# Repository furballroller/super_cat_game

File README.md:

# super_cat_game

> [!CAUTION]
> The current hardware version is [hardware_v1](hardware_v1)!! Anyway, is my first PCB project, so neither version is very good. It may be cost-inefficient and buggy.

> [!WARNING]
> **if regenerating production files from KICAD, the LCSC Part # in the BOM and component orientations in CPL may be incorrect. Make sure to double check part numbers and orientation in JLCPCB before paying** I don't know how to fix it and had to directly edit BOM.csv :<

> [!TIP]
> these banners are so cool lol

_Final product:_

- [_3D-printed case on Onshape_](https://cad.onshape.com/documents/4ded436d6b7f683e9c68b6fa/w/fe5cc562122e090332767be7/e/b2ba9b935da609d900851709?renderMode=0&uiState=6a58e4a5db7545b8e7dbac50) (proper assembly instructions below)
- [_KiCAD Project_](hardware_v1)
- [_Arduino Sketches_](software) (PlatformIO IDE)

Cat silhouette traced from this photo: ID <a href="https://www.dreamstime.com/cat-mid-air-jump-white-coloured-patches-jumping-down-against-yellow-wall-image115652480">115652480</a> @ <a href="https://www.dreamstime.com/lazaroctavian_info">Octavian Mihai Lazar</a> | <a href="https://www.dreamstime.com/">Dreamstime.com</a>

## backstory

So basically my friend had a cat, and I was just getting into arduino electronics, so I wanted to make a chasing game for the both of them! I ended up deciding on a pressure-sensitive LED mat, for an interactive laser-pointer kind-of game, with wifi connectivity for convenience. It could be nice to use regularly to keep your pets fit, but really this is just a fun beginner project to me.

Then, in between reels, I discovered Fallout, a 2026 hardware hackathon for 13-18yos backed by Hack Club. I was drawn in by the promise of full project funding and a free trip to Shenzhen, and was enthralled by the experienced and helpful community ready to help. I would highly recommend Hack Club hackathons like this if you're new/intermediate like me and within the age range :>

The scope expanded when I realised that there's so much more potential with my setup! I used a powerful ESP32 S3 N16R8 Devkit, so I broke out the pins for prototyping. You can hook up any peripherals you want for your game! Like, with a [3D printed kibble dispenser](https://electronoobs.com/tutorial/3d-printed-arduino-cat-feeder), you could implement scheduled feeding and dispense treats as an in-game currency :>

But you can program anything, not just for a cat! Chess online/locally would be easy and super fun! Maybe even something like [Osu](https://osu.ppy.sh/), make use of the full spectrum of colours! You might even want to host an online multiplayer game...

## overview

This project hardwires a pressure-sensitive LED mat to a powerful general-purpose devkit, intended for making inuitive arcade-style games (for a cat, if you'd like! :> )

I used Arduino to code up a simple cat game ([Arduino sketch](software/cat_game)), where a laser dot darts around, avoids people, and resets the game when caught. To use this, just upload the code to the devkit (using it's built-in USB-C port), plug it into the PCB, then plug the PCB into the wall!

The devkit opens the project to endless posibilities, including bluetooth game controllers, network games, and over-the-air coding for easy game dev ([template Arduino sketch with ArduinoOTA](software/template+OTA)). This project is meant to function as a very cool extension of the microcontroller, for those who might want to jump straight into making games using this touch interface.

### specs

- ~45*45cm play area
  - 14*14 Velostat pressure sensor matrix
  - 13*13 WS2812B LED matrix (very low resolution tho)
- Wifi/Bluetooth capability
  - Cheap ESP32 S3 N16R8 Devkit clone off [AliExpress](https://www.aliexpress.com/item/1005008790513258.html)
- Broken-out devkit pins and 5V power supply for any peripherals you might like to add
  - e.g. [3D printed kibble dispenser](https://electronoobs.com/tutorial/3d-printed-arduino-cat-feeder)

### cost

[Overall BOM.csv](bom.csv) | [PCB BOM.csv](hardware_v1/production/bom.csv)

The overall BOM represents what I plan to order: 5 populated PCB boards (JLCPCB minimum order quantity), but only 1 housing/mat/devkit. Though, I did include a laptop charger and the LED strips that I already have. This comes out to 111.83 USD.

I didn't include tools (not consumed) like soldering equipment and a 3D printer, but I did approximate the cost of consumables like solder, tape rolls, screws and filament.

#### Per unit

|Cost (USD)|Stuff|
|--|--|
|14.11|Power supply|
|22.15|Electronics|
|2.32|Housing|
|33.32|Mat|

Excluding shipping, it's about 71.90 USD per unit.

<!--
## big_picture
the mat should roll up

-->

### hardware

<!-- a flowchart -->

I decided to use a USBC PD laptop charger as the PSU since it's quite common and versatile and it's not too expensive.

The velostat matrix is connected with two 45cm lengths of 16-way IDC cables (not shown in CAD). One individual line will be cut, stripped, and stuck to the sensor lines at regular intervals along the mat, 14 horizontally and 14 vertically. There's more detail in the assembly walkthrough below.

#### Velostat pressure sensor matrix

The rest of the system is quite self-explanatory except for the Velostat pressure sensor matrix, so I'll try my best to explain. There's a good video of it by [MarcoReps on YouTube](https://www.youtube.com/watch?v=0uPZwMg5B3k).

Velostat is a thin plastic sheet with electrical resistance that decreases as it is pressed or deformed.

Each "sensor" works by sandwiching a square of Velostat between perpendicular strips of conductive fabric tape, such that it acts as a resistor between them.

When the Velostat is compressed, the resistance between the two strips decreases. Connecting one tape to 3.3V through a normal resistor (e.g. 10k Ohms) and the other to GND, the circuit becomes a voltage divider between the Velostat and the normal resistor. The microcontroller can read the voltage at this point (relative to GND) to figure out the resistance of the Velostat, which tells you approximately how much pressure is on it!

Along one long conductive strip, multiple perpendicular strips can be laid across with Velostat between, creating a line of sensors. By connecting all the perpendicular lines to a multiplexer's channels, they are all left in a high-impedance state except the selected channel. The normal resistor and ADC pin can be connected on the single output of the multiplexer, so they can be reused when the channel is switched.

Conventional diagram

Another way to show the same circuit:

The matrix in the mat is 14 conductive lines crossed with 14 perpendicular lines, making a total of 14^2=196 "sensors." It's the same as the line of sensors, but there are multiple lines of sensors, with one ground connection each. The ground connections are controlled by another multiplexer, only allowing one line to be active at once.

This is a 4 by 4 example. Multiplexer 1 picks the line of sensors connected to GND, and multiplexer 2 picks the sensor from that line to read.

The real mat works using two 16 channel multiplexers (CD74HC4067) on the PCB: the ESP32 specifies a channel, the multiplexers switch to the corresponding Velostat sensor, then the ESP32 takes a reading through it's ADC pin. Instead of the normal resistor, there is a potentiometer (variable resistor) that allows you to adjust sensitivity.

This is how the sensors are tiled

### code

[My example sketches:](software) (currently untested)

- [press_light](software/press_light): intended to be a test of function, that should simply light up LEDs around where you press. This would be great for making sure the hardware is behaving, or as a fun starting point if you want to experiment with code and get the hang of Arduino.
- [cat_game](software/cat_game): a simple cat game where the computer controls a red laser-pointer-like dot to avoid people.
- [template](software/template): an empty template for your project! I set up some useful functions in functions.cpp and put all the initialisation code in for you.
- [template+OTA](software/template+OTA): same as [template](software/template), but I also set up [ArduinoOTA](https://github.com/JAndrassy/ArduinoOTA). I think it's really cool that you can upload code wirelesly like magic! ([a cool tutorial page](https://www.programmingelectronics.com/arduinoota/))

I used PlatformIO on Visual Studio Code to write my Arduino programs for the microcontroller. This may sound convoluted, but I did it this way because Arduino programs are easy to write (compared to industrial languages) but Arduino IDE is horrible!

If you want to use Arduino IDE, you can quite easily copy-paste my code into the IDE. For a given project folder in [software](software), you just kinda paste the stuff from functions.cpp first, then the stuff from main.cpp... it may take a bit of fiddling around though, so I would recommend looking into PlatformIO (after getting used to it, I find it way way better :>)

I used [FastLED](https://github.com/fastled/fastled) to control the WS2812B neopixels

## assembly

<!--    -->

I thought it was cool to include the little thumb, and the vents are accurate too! They're like LHS/RHS prints from a cat grabbing the case or something :>
Also, the USB port is on a 45 degree angle so the wire leaves perpendicular to the mat.

I'll touch on the key features of the design below. For more info, see the 3D model for this is in [my Onshape doc](https://cad.onshape.com/documents/4ded436d6b7f683e9c68b6fa/w/fe5cc562122e090332767be7/e/b2ba9b935da609d900851709?renderMode=0&uiState=6a58e4a5db7545b8e7dbac50), under the tab "boxV1"
(my bad for the bad organisation, I'm still learning CAD)  

If you want to change the tolerances (they're untested), I haven't tried, sorry if something is inaccurate. It may be best to change the tolerances in your slicer.
> [!TIP]
> the Onshape link might not work. I had to click it, then **Ctrl+X Ctrl+V Enter** from the address bar

### electronics

I contained the circuit in a PCB attached to the corner of the mat, and I've also desgined a 3D-printed housing for it.

The whole project runs off an ESP32 S3 N16R8 microcontroller devkit, which is like an Arduino but better (in my opinion)

[On Aliexpress](https://www.aliexpress.com/item/1005008790513258.html)
(**I would recommend getting "S3 KIT" because the screw terminals are very handy, but I put the board by itself into the BOM**)

When choosing a microcontroller, I noticed that a lot of clone (knockoff) ESP32 S3 devkits, including the one I bought, have the antenna port but also an antenna built into the PCB. I think they give you the option to change to an external antenna by doing a bit of soldering, but by default it is connected to the onboard antenna.

#### PCB

<!--    -->

> [!CAUTION]
>
> - Ignore the capacitor going off the edge, the EasyEDA model is wrong
> - The two parallel rows of vertical pin headers (for the devkit) should be female, again the EasyEDA model is wrong

About the design:

- JL1 and JR1 hold the ESP32 devkit
- The USB-C is for power only
- JLED1 is for the LED strip
- JPWR1 is 5V power for any peripherals you might want to add
- The IDC sockets are for the pressure-sensing data lines
- The fancy ICs are just CD74HC4067 multiplexers for selecting the pressure-sensing channel to read
- The potentiometer is for adjusting the sensitivity of the pressure sensing (it's part of a voltage divider)
- U1 is a logic level converter for the LEDs.

Regarding soldering: I designed the PCB to be hand-soldered, hence the abundance of THT and the large 0805 capacitors/resistors. My only concerns are the SSOP 74HC4067 and 6-pin USB-C port, but other than that the rest should be beginner friendly, from what I can gather. I'm thinking of going to my local makerspace to solder this. In Melbourne, Library at the Dock has one equipped with a digital microscope, flux/solder/wick, and  Hakko FX-888 soldering stations, all free of charge. Maybe be careful around ESD, I'll update on my degree of success when I build it.

#### housing

<!--  -->

I'm not very good at 3D CAD either, but this should work... I think  
The design is quite self-explanatory, but below are some key features that I thought I should highlight:

On the base, there is a cutout for those holes on the mat. The holes are truncated cones, inspired by [this video by BV3D](https://youtu.be/zaphoWIwSGI). 
I designed my case to work with 3M screws, and the truncated cones means you can use machine screws or self-tapping (I think)

The base supports the PCB with a few stilts through the holes in the PCB, again using M3 truncated cones. The smaller stilts give some support to the IDC connectors, which I expect may require some force to plug in and out.

The top fits on the bottom with M3 screws, and features holes for IDC, the LED strip, the USB-C power port, optional 5V power lines, and the broken-out GPIO from the devkit. Also there are (very stylish) vents :>

There's also a lid that slides onto the top, so the devkit is protected but can be accessed easily during game development. 
I included a cool thinner section where the onboard LED is, so the status light should look like a cat's paw.

### sensor_mat

> [!TIP]
> You'll see two holes in the top-right corner of the mat. These fit M3 screw heads, and should help anchor the PCB to the mat.

1. The LED strips

I used 13 LED long sections of 30 LED/m WS2812B individually addressable LEDs
With pads on either side, each section is about 43.333mm long (theoretically)  
[Similar product on AliExpress](https://www.aliexpress.com/item/1005007989207832.html)
(**MAKE SURE THE SPACING IS 30 LEDs/m; I'd recommend buying 2 "3m 30 IP30"**)

There are 13 of these sections, forming a 13*13 grid (169 LEDs)
The ends can be soldered together with jumper wires, preferably with stranded wire, like so:

<figure>

	<figcaption>(don't crease too much tho!)</figcaption>
</figure>

2. The popsicle sticks  

I used 2mm thick, 18mm wide popsicle sticks (jumbo craft sticks)  
[My local option (Australia)](https://www.officeworks.com.au/shop/officeworks/p/kadink-jumbo-craft-sticks-natural-50-pack-showk0137)

In the CAD, I made very long, 18mm-wide rectangles for simplicity. 
They represent the area that should be filled with popsicle sticks. 
It may be useful to trim off the rounded ends for a fuller surface, but the space could alternatively be filled with hot glue for better adhesion.

They will be adhered together with the conductive tape that goes on top (see below). 
They should be adhered to the LED strip with high-temperature hot glue or silicone (not being lazy! it's good for sticking to wood and flex-PCB, trust). 
Please ensure hot glue doesn't get under the popsicle sticks, as this may affect the pressure detection and make the mat lumpy. 

<figure>  
	 
	<figcaption>Try smushing the glue into the corner where the edge of the popsicle sticks meets the LED's flex-PCB</figcaption>
</figure>

3. Conductive fabric tape (bottom)  

I used 0.1mm thick, 8mm wide conductive fabric tape. This acts as the bottom layer of the velostat matrix.  
[Similar product on AliExpress](https://www.aliexpress.com/item/1005007568611729.html)  
(**I'd recommend buying 1 "8mm"**)

The tape sticks onto the wood to connect it together. If this isn't sturdy enough, the sticks can keep their rounded ends, and hot glue can help hold them together (in the gap made by the rounded ends)

An IDC wire needs to be attached to one end of each strip, so I recommend the following:

Leave a 1-2cm tape overhang

Peel the stripped IDC wire away from the rest and press it here. for extra security, you could wrap the tape around the entire row of IDC wires.

Press another section of tape here, sticking the sticky sides together and securing the wire's insulation and popsicle stick together

Wrap the main tape over the other strip and the wire (ensure it has contact with both the insulation and the bare metal, and press it into the crevices and flush to the bottom of the mat

4. Velostat

I used a 0.1mm thick, 280mm square sheet of velostat, cut up into ~18mm squares (this stuff is expensive!!)  
[My local option (Australia)](https://www.pakronics.com.au/products/pressure-sensitive-conductive-sheet-velostat-linqstat-ada1361)

The squares will be adhered to the popsicles with thin-film double-sided tape, with two 4mm wide sections flanking the conductive tape running down the middle of the popsicles.

It is important that the tape is as thin or thinner than the velostat (≤0.1mm), or it may squish instead of the velostat, lowering the sensitivity, and so resolution, of pressure readings.

[Double-sided tape on AliExpress](https://www.aliexpress.com/item/1005012157309588.html)  
(**I'd recommend buying 1 "5mm"**)

5. Conductive fabric tape (top)

This layer is sticky-side-up, so in real life you would stick it onto the top EVA first (see below). Please make sure the tape is aligned such that it doesn't touch the bottom layer directly anywhere, only conducting through the Velostat squares.

An IDC wire needs to be attached just like in the other layer, so I would recommend the same strategy, but wrapped upwards around the EVA. The ugly tape overhangs on top of the EVA will be covered by electrical tape later.

6. Frosted plastic sheet (EVA)

I used a ~1mm thick, 450mm square of EVA plastic intended to line drawers.  
[My local option (Australia)](https://www.rejectshop.com.au/p/drawer-and-shelf-liner-45x150cm)

The top layer of conductive tape should be stuck to the bottom of this sheet, on the smooth side. This EVA layer can be adhered to the bottom construction with electrical tape, not just because it's easy to design, but because of it's suitable properties. The mat is designed to loosely roll up for easy transport/storage, requiring flexibility, and the edges must be soft to keep flying fingers/paws safe around the mat :)

## the_past

> [!CAUTION]
> I cobbled V0 together from backups so maybe double check whether it works if you plan to build it. e.g. there's no copper exclusion around the antenna :<

Just a quick note about the [hardware_v0](hardware_v0) and [hardware_v1](hardware_v1), I just uploaded v0 so you can see a previous design I made. I wanted to preserve more ESP32 GPIO pins, so I used counter ICs to cycle through the MUX channels of the sensor grid. This would've allowed me to step through each channel with just one clock pin per counter, compared to the 4 pins per counter I would've needed to control the MUX channel directly. It wouldn't have added much time either, as the counter works even faster than a digitalWrite()! Sending one clock pulse might even be more efficient than using Arduino to update the state of 4 pins... anyway, I decided to remove the counters in V1 to save board space and money, seeing as there are so many available GPIO anyway lol :>

## the_future

Some ideas I have:

- multiplexing/charlieplexing/shift registers with regular LEDs to replace expensive neopixels
- using an ESP32 S3 WROOM SOC module for a smaller and cheaper PCB
- using a library like NeoPixelBus instead of FastLED to make the Arduino code faster/efficient
- somehow allowing IDC to attach/detatch without needing to unscrew the lid, for portability/storage

Lemme know if you've got any suggestions!
My email: [aydeny8k@gmail.com](mailto:aydeny8k@gmail.com)

## references

The Velostat pressure matrix idea: [Youtube video by MarcoReps](https://www.youtube.com/watch?v=0uPZwMg5B3k)

Truncated-cone screw holes idea: [Youtube video by BV3D](https://youtu.be/zaphoWIwSGI)

Sliding lid shape: [Wuodan0 on Thingiverse](https://www.thingiverse.com/thing:5201077)

[FastLED](https://github.com/fastled/fastled) Arduino library

[ArduinoOTA](https://github.com/JAndrassy/ArduinoOTA) Arduino library

[easyeda2kicad.py](https://github.com/uPesy/easyeda2kicad.py) Python script

Pictures annotated in Google Drawings

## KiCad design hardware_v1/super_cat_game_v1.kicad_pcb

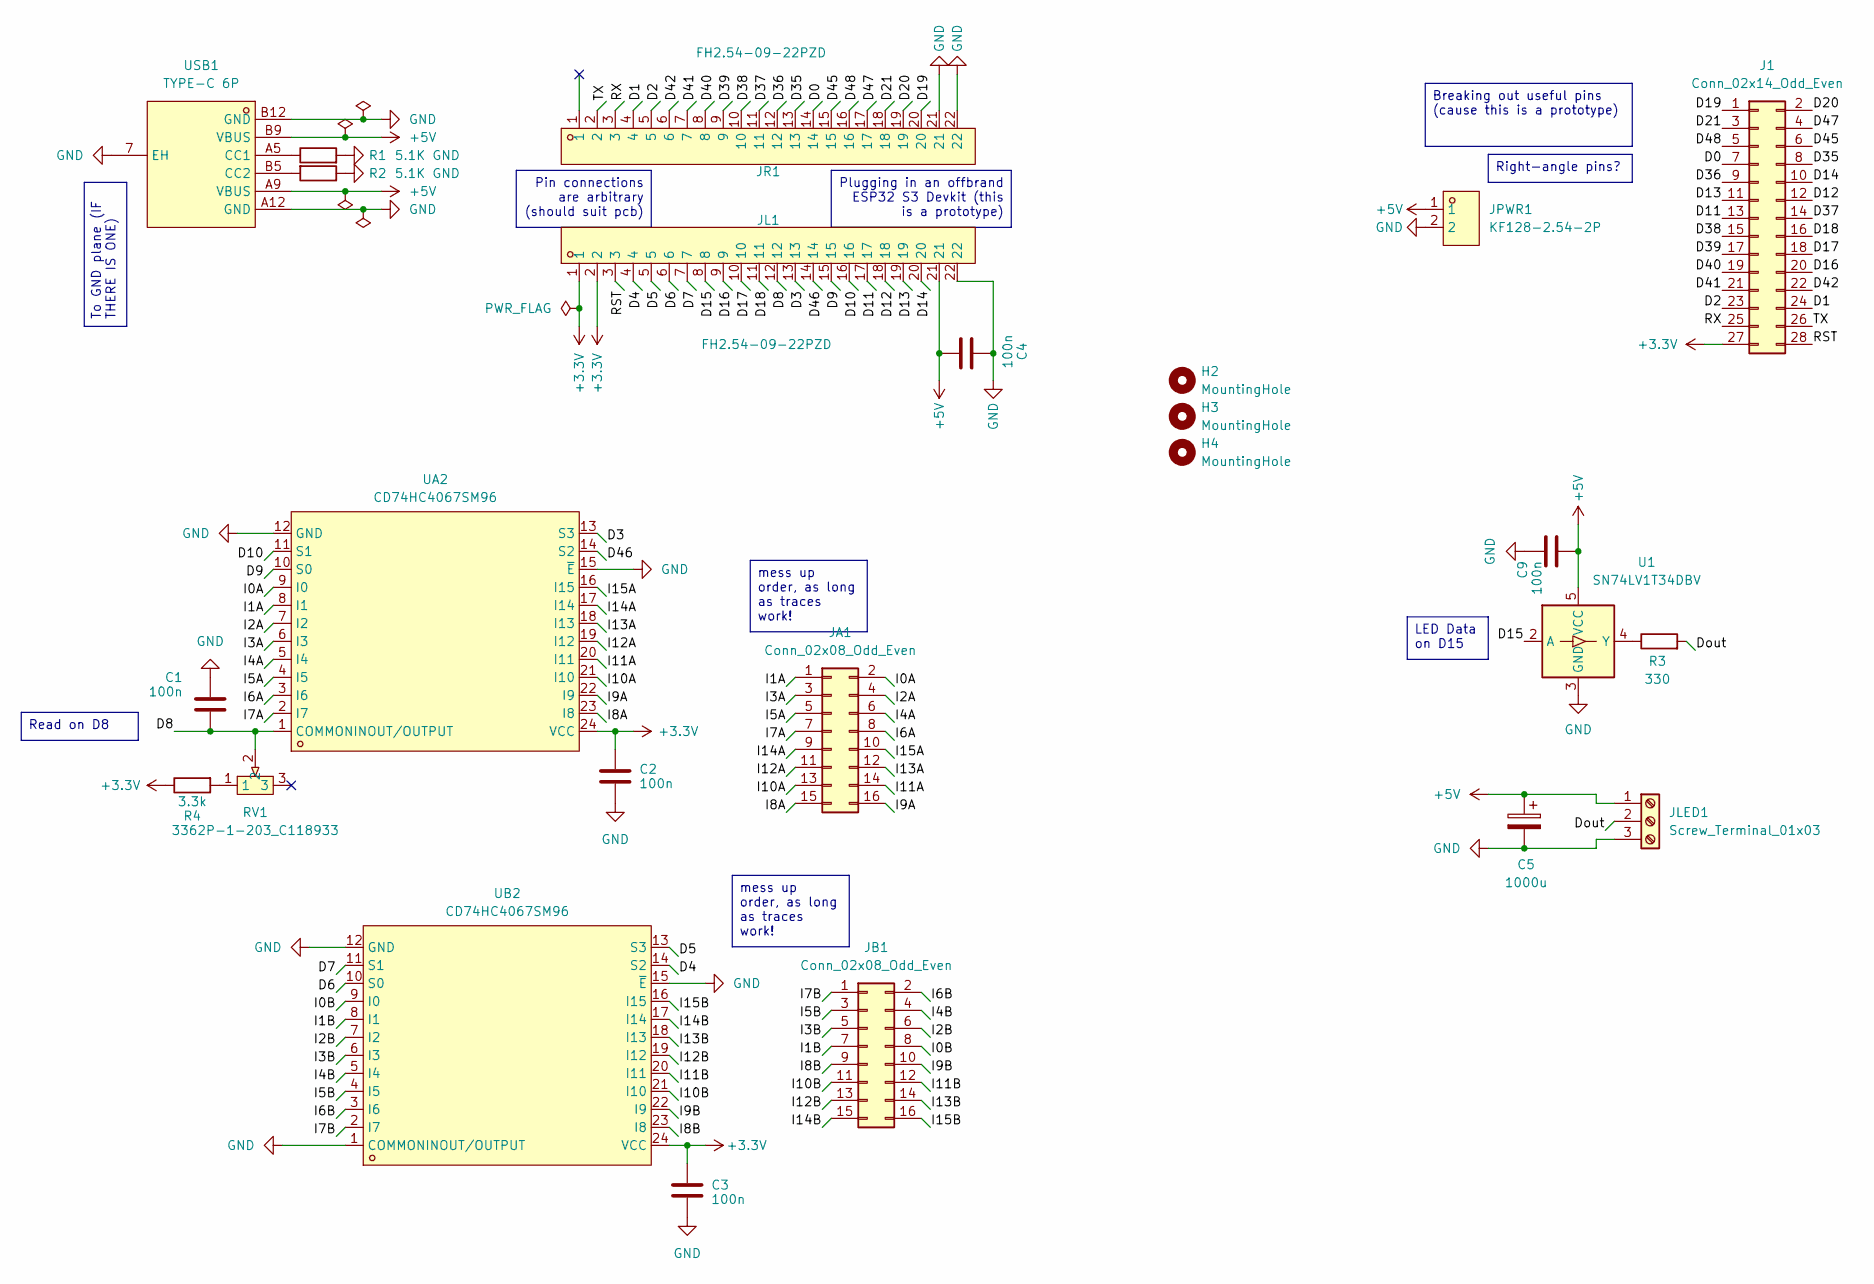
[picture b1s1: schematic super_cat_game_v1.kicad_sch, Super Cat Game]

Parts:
C1, C2, C3, C9: 100n; C_0805_2012Metric_Pad1.18x1.45mm_HandSolder; JLC_3DModel 32fe2cf9314f444ca2785a33c2db7189
C4: 100n; C_0805_2012Metric_Pad1.18x1.45mm_HandSolder; LCSC Part C28233
C5: 1000u; cap_flat; JLC_3DModel fb7e59b4bf4a464e9052b6d7cde2fdda
H2, H3, H4: MountingHole; MountingHole_3.2mm_M3
J1: Conn_02x14_Odd_Even; HDR-TH_28P-P2.54-H-M-R2-C14-S2.54; LCSC Part C725926
JA1: Conn_02x08_Odd_Even; IDC-TH_16P-P2.54_C3406; JLC_3DModel 20dc7cf4168b42d3ab78a2412575e9e9
JB1: Conn_02x08_Odd_Even; IDC-TH_16P-P2.54_C3406; JLC_3DModel 20dc7cf4168b42d3ab78a2412575e9e9
JL1: FH2.54-09-22PZD; HDR-TH_22P-P2.54-V-M; MPN FH2.54-09-22PZD; LCSC Part C7500786
JLED1: Screw_Terminal_01x03; CONN-TH_3P-P2.54_KF128-2.54-3P; JLC_3DModel a3f15aa9d36b4fa2b870b9dbfce89390
JPWR1: KF128-2.54-2P; CONN-TH_P2.54_KF128-2.54-2P; MPN KF128-2.54-2P; LCSC Part C474920
JR1: FH2.54-09-22PZD; HDR-TH_22P-P2.54-V-M; MPN FH2.54-09-22PZD; LCSC Part C7500786
R1, R2: 5.1K; R_0805_2012Metric_Pad1.20x1.40mm_HandSolder; LCSC Part C27834
R3: 330; R_0805_2012Metric_Pad1.20x1.40mm_HandSolder; LCSC Part C17630
R4: 3.3k; R_0805_2012Metric_Pad1.20x1.40mm_HandSolder; LCSC Part C26020
RV1: 3362P-1-203_C118933; RES-ADJ-TH_3P-L7.1-W6.9-P2.50-L_3362P; MPN 3362P-1-203; LCSC Part C118933
U1: SN74LV1T34DBV; SOT-23-5_HandSoldering; LCSC Part C100024
UA2: CD74HC4067SM96; SSOP-24_L8.1-W5.3-P0.65-LS7.8-BL; MPN CD74HC4067SM96; LCSC Part C98457
UB2: CD74HC4067SM96; SSOP-24_L8.1-W5.3-P0.65-LS7.8-BL; MPN CD74HC4067SM96; LCSC Part C98457
USB1: TYPE-C 6P; TYPE-C-SMD_TYPE-C-6P_1; MPN TYPE-C 6P; LCSC Part C456012

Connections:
+3.3V: C2.1, C3.1, J1.27, JL1.1, JL1.2, R4.1, UA2.24 (VCC), UB2.24 (VCC)
+5V: C4.2, C5.1, C9.1, JL1.21, JLED1.1, JPWR1.1, U1.5 (VCC), USB1.A9 (VBUS), USB1.B9 (VBUS)
/D0: J1.7, JR1.14
/D1: J1.24, JR1.4
/D2: J1.23, JR1.5
/D3: JL1.13, UA2.13 (S3)
/D4: JL1.4, UB2.14 (S2)
/D5: JL1.5, UB2.13 (S3)
/D6: JL1.6, UB2.10 (S0)
/D7: JL1.7, UB2.11 (S1)
/D8: C1.1, JL1.12, RV1.2, UA2.1 (COMMONINOUT/OUTPUT)
/D9: JL1.15, UA2.10 (S0)
/D10: JL1.16, UA2.11 (S1)
/D11: J1.13, JL1.17
/D12: J1.12, JL1.18
/D13: J1.11, JL1.19
/D14: J1.10, JL1.20
/D15: JL1.8, U1.2 (A)
/D16: J1.20, JL1.9
/D17: J1.18, JL1.10
/D18: J1.16, JL1.11
/D19: J1.1, JR1.20
/D20: J1.2, JR1.19
/D21: J1.3, JR1.18
/D35: J1.8, JR1.13
/D36: J1.9, JR1.12
/D37: J1.14, JR1.11
/D38: J1.15, JR1.10
/D39: J1.17, JR1.9
/D40: J1.19, JR1.8
/D41: J1.21, JR1.7
/D42: J1.22, JR1.6
/D45: J1.6, JR1.15
/D46: JL1.14, UA2.14 (S2)
/D47: J1.4, JR1.17
/D48: J1.5, JR1.16
/Dout: JLED1.2, R3.2
/I0A: JA1.2, UA2.9 (I0)
/I0B: JB1.8, UB2.9 (I0)
/I1A: JA1.1, UA2.8 (I1)
/I1B: JB1.7, UB2.8 (I1)
/I2A: JA1.4, UA2.7 (I2)
/I2B: JB1.6, UB2.7 (I2)
/I3A: JA1.3, UA2.6 (I3)
/I3B: JB1.5, UB2.6 (I3)
/I4A: JA1.6, UA2.5 (I4)
/I4B: JB1.4, UB2.5 (I4)
/I5A: JA1.5, UA2.4 (I5)
/I5B: JB1.3, UB2.4 (I5)
/I6A: JA1.8, UA2.3 (I6)
/I6B: JB1.2, UB2.3 (I6)
/I7A: JA1.7, UA2.2 (I7)
/I7B: JB1.1, UB2.2 (I7)
/I8A: JA1.15, UA2.23 (I8)
/I8B: JB1.9, UB2.23 (I8)
/I9A: JA1.16, UA2.22 (I9)
/I9B: JB1.10, UB2.22 (I9)
/I10A: JA1.13, UA2.21 (I10)
/I10B: JB1.11, UB2.21 (I10)
/I11A: JA1.14, UA2.20 (I11)
/I11B: JB1.12, UB2.20 (I11)
/I12A: JA1.11, UA2.19 (I12)
/I12B: JB1.13, UB2.19 (I12)
/I13A: JA1.12, UA2.18 (I13)
/I13B: JB1.14, UB2.18 (I13)
/I14A: JA1.9, UA2.17 (I14)
/I14B: JB1.15, UB2.17 (I14)
/I15A: JA1.10, UA2.16 (I15)
/I15B: JB1.16, UB2.16 (I15)
/RST: J1.28, JL1.3
/RX: J1.25, JR1.3
/TX: J1.26, JR1.2
GND: C1.2, C2.2, C3.2, C4.1, C5.2, C9.2, JL1.22, JLED1.3, JPWR1.2, JR1.21, JR1.22, R1.2, R2.1, U1.3 (GND), UA2.12 (GND), UA2.15 (~E), UB2.1 (COMMONINOUT/OUTPUT), UB2.12 (GND), UB2.15 (~E), USB1.7 (EH), USB1.A12 (GND), USB1.B12 (GND)
unnamed: R4.2, RV1.1
unnamed: R3.1, U1.4 (Y)
unnamed: R1.1, USB1.A5 (CC1)
unnamed: R2.2, USB1.B5 (CC2)

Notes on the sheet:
To GND plane (IF THERE IS ONE)
mess up order, as long as traces work!
Breaking out useful pins (cause this is a prototype)
Read on D8
Right-angle pins?
Plugging in an offbrand ESP32 S3 Devkit (this is a prototype)
LED Data on D15
Pin connections are arbitrary (should suit pcb)

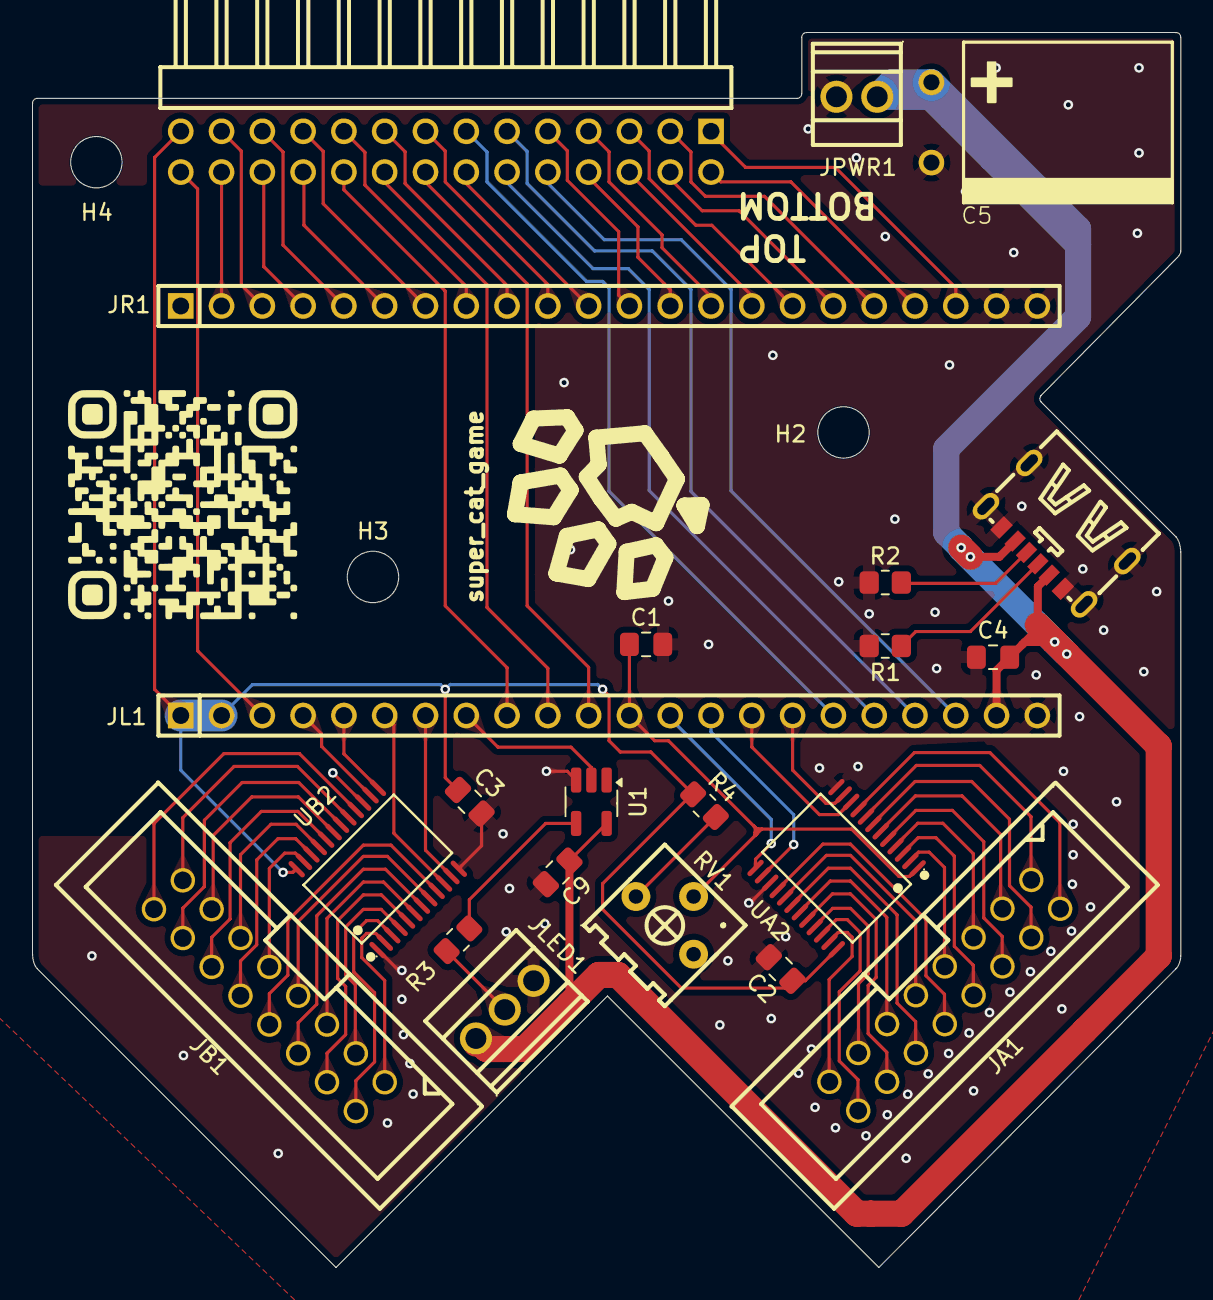
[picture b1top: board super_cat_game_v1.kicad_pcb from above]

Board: 2 copper layers, 71.5 x 76.9 mm, 25 parts (0 on the bottom side), 77 nets.

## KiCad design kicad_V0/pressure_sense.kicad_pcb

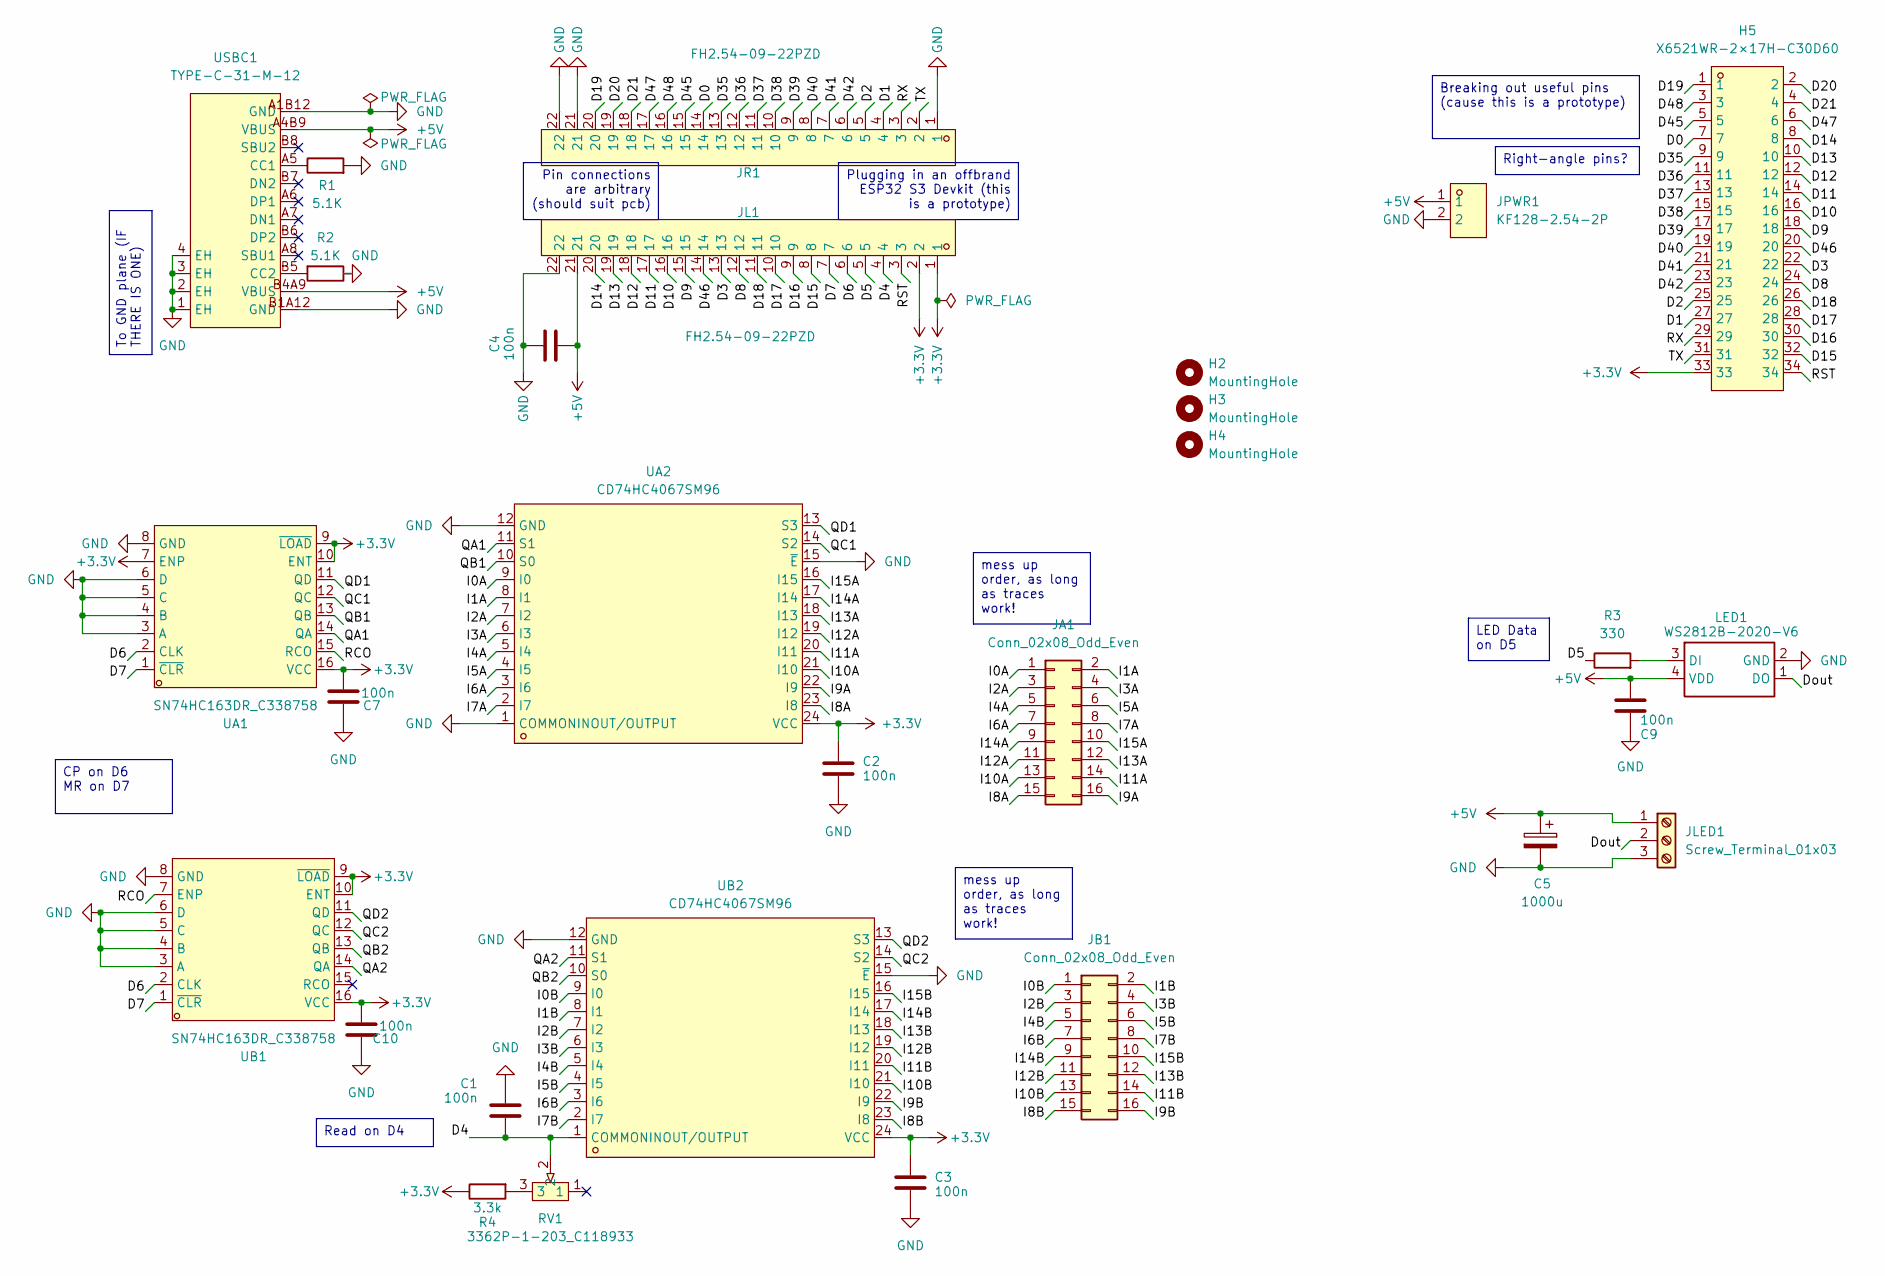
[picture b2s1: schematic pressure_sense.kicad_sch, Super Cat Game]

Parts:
C1, C2, C3, C7, C9, C10: 100n; C0402; JLC_3DModel 32fe2cf9314f444ca2785a33c2db7189
C4: 100n; C0402; LCSC Part # C1525
C5: 1000u; CAP-TH_BD10.0-P5.00-D0.6-FD; JLC_3DModel fb7e59b4bf4a464e9052b6d7cde2fdda
H2, H3, H4: MountingHole; MountingHole_3.2mm_M3
H5: X6521WR-2×17H-C30D60; HDR-TH_34P-P2.54-H-M-R2-C17-S2.54; MPN X6521WR-2x17H-C60D30; LCSC Part # C725929
JA1: Conn_02x08_Odd_Even; IDC-TH_16P-P2.54_C3406; JLC_3DModel 20dc7cf4168b42d3ab78a2412575e9e9
JB1: Conn_02x08_Odd_Even; IDC-TH_16P-P2.54_C3406; JLC_3DModel 20dc7cf4168b42d3ab78a2412575e9e9
JL1: FH2.54-09-22PZD; HDR-TH_22P-P2.54-V-M; MPN FH2.54-09-22PZD; LCSC Part # C7500786
JLED1: Screw_Terminal_01x03; CONN-TH_3P-P2.54_KF128-2.54-3P; JLC_3DModel a3f15aa9d36b4fa2b870b9dbfce89390
JPWR1: KF128-2.54-2P; CONN-TH_P2.54_KF128-2.54-2P; MPN KF128-2.54-2P; LCSC Part # C474920
JR1: FH2.54-09-22PZD; HDR-TH_22P-P2.54-V-M; MPN FH2.54-09-22PZD; LCSC Part # C7500786
LED1: WS2812B-2020-V6; LED-SMD_4P-L2.2-W2.0-P1.00_WS2815C-2020-4P; Manufacturer Part WS2812B-2020-V6; LCSC Part # C52917434
R1, R2: 5.1K; R_0402_1005Metric; LCSC Part # C25905
R3: 330; R_0402_1005Metric; LCSC Part # C25104
R4: 3.3k; R_0402_1005Metric; LCSC Part # C25890
RV1: 3362P-1-203_C118933; RES-ADJ-TH_3P-L7.1-W6.9-P2.50-L_3362P; MPN 3362P-1-203; LCSC Part # C118933
UA1: SN74HC163DR_C338758; SOIC-16_L9.9-W3.9-P1.27-LS6.0-BL; MPN SN74HC163DR; LCSC Part # C338758
UA2: CD74HC4067SM96; SSOP-24_L8.1-W5.3-P0.65-LS7.8-BL; MPN CD74HC4067SM96; LCSC Part # C98457
UB1: SN74HC163DR_C338758; SOIC-16_L9.9-W3.9-P1.27-LS6.0-BL; MPN SN74HC163DR; LCSC Part # C338758
UB2: CD74HC4067SM96; SSOP-24_L8.1-W5.3-P0.65-LS7.8-BL; MPN CD74HC4067SM96; LCSC Part # C98457
USBC1: TYPE-C-31-M-12; USB-C_SMD-TYPE-C-31-M-12_1; MPN TYPE-C-31-M-12; LCSC Part # C165948

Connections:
+3.3V: C2.1, C3.1, C7.1, C10.1, H5.33, JL1.1, JL1.2, R4.1, UA1.7 (ENP), UA1.9 (~LOAD), UA1.10 (ENT), UA1.16 (VCC), UA2.24 (VCC), UB1.9 (~LOAD), UB1.10 (ENT), UB1.16 (VCC), UB2.24 (VCC)
+5V: C4.2, C5.1, C9.1, JL1.21, JLED1.1, JPWR1.1, LED1.4 (VDD), USBC1.A4B9 (VBUS), USBC1.B4A9 (VBUS)
/D0: H5.7, JR1.14
/D1: H5.27, JR1.4
/D2: H5.25, JR1.5
/D3: H5.22, JL1.13
/D4: C1.1, JL1.4, RV1.2, UB2.1 (COMMONINOUT/OUTPUT)
/D5: JL1.5, R3.1
/D6: JL1.6, UA1.2 (CLK), UB1.2 (CLK)
/D7: JL1.7, UA1.1 (~CLR), UB1.1 (~CLR)
/D8: H5.24, JL1.12
/D9: H5.18, JL1.15
/D10: H5.16, JL1.16
/D11: H5.14, JL1.17
/D12: H5.12, JL1.18
/D13: H5.10, JL1.19
/D14: H5.8, JL1.20
/D15: H5.32, JL1.8
/D16: H5.30, JL1.9
/D17: H5.28, JL1.10
/D18: H5.26, JL1.11
/D19: H5.1, JR1.20
/D20: H5.2, JR1.19
/D21: H5.4, JR1.18
/D35: H5.9, JR1.13
/D36: H5.11, JR1.12
/D37: H5.13, JR1.11
/D38: H5.15, JR1.10
/D39: H5.17, JR1.9
/D40: H5.19, JR1.8
/D41: H5.21, JR1.7
/D42: H5.23, JR1.6
/D45: H5.5, JR1.15
/D46: H5.20, JL1.14
/D47: H5.6, JR1.17
/D48: H5.3, JR1.16
/Dout: JLED1.2, LED1.1 (DO)
/I0A: JA1.1, UA2.9 (I0)
/I0B: JB1.1, UB2.9 (I0)
/I1A: JA1.2, UA2.8 (I1)
/I1B: JB1.2, UB2.8 (I1)
/I2A: JA1.3, UA2.7 (I2)
/I2B: JB1.3, UB2.7 (I2)
/I3A: JA1.4, UA2.6 (I3)
/I3B: JB1.4, UB2.6 (I3)
/I4A: JA1.5, UA2.5 (I4)
/I4B: JB1.5, UB2.5 (I4)
/I5A: JA1.6, UA2.4 (I5)
/I5B: JB1.6, UB2.4 (I5)
/I6A: JA1.7, UA2.3 (I6)
/I6B: JB1.7, UB2.3 (I6)
/I7A: JA1.8, UA2.2 (I7)
/I7B: JB1.8, UB2.2 (I7)
/I8A: JA1.15, UA2.23 (I8)
/I8B: JB1.15, UB2.23 (I8)
/I9A: JA1.16, UA2.22 (I9)
/I9B: JB1.16, UB2.22 (I9)
/I10A: JA1.13, UA2.21 (I10)
/I10B: JB1.13, UB2.21 (I10)
/I11A: JA1.14, UA2.20 (I11)
/I11B: JB1.14, UB2.20 (I11)
/I12A: JA1.11, UA2.19 (I12)
/I12B: JB1.11, UB2.19 (I12)
/I13A: JA1.12, UA2.18 (I13)
/I13B: JB1.12, UB2.18 (I13)
/I14A: JA1.9, UA2.17 (I14)
/I14B: JB1.9, UB2.17 (I14)
/I15A: JA1.10, UA2.16 (I15)
/I15B: JB1.10, UB2.16 (I15)
/QA1: UA1.14 (QA), UA2.11 (S1)
/QA2: UB1.14 (QA), UB2.11 (S1)
/QB1: UA1.13 (QB), UA2.10 (S0)
/QB2: UB1.13 (QB), UB2.10 (S0)
/QC1: UA1.12 (QC), UA2.14 (S2)
/QC2: UB1.12 (QC), UB2.14 (S2)
/QD1: UA1.11 (QD), UA2.13 (S3)
/QD2: UB1.11 (QD), UB2.13 (S3)
/RCO: UA1.15 (RCO), UB1.7 (ENP)
/RST: H5.34, JL1.3
/RX: H5.29, JR1.3
/TX: H5.31, JR1.2
GND: C1.2, C2.2, C3.2, C4.1, C5.2, C7.2, C9.2, C10.2, JL1.22, JLED1.3, JPWR1.2, JR1.1, JR1.21, JR1.22, LED1.2 (GND), R1.2, R2.1, UA1.3 (A), UA1.4 (B), UA1.5 (C), UA1.6 (D), UA1.8 (GND), UA2.1 (COMMONINOUT/OUTPUT), UA2.12 (GND), UA2.15 (~E), UB1.3 (A), UB1.4 (B), UB1.5 (C), UB1.6 (D), UB1.8 (GND), UB2.12 (GND), UB2.15 (~E), USBC1.1 (EH), USBC1.2 (EH), USBC1.3 (EH), USBC1.4 (EH), USBC1.A1B12 (GND), USBC1.B1A12 (GND)
unnamed: LED1.3 (DI), R3.2
unnamed: R4.2, RV1.3
unnamed: R1.1, USBC1.A5 (CC1)
unnamed: R2.2, USBC1.B5 (CC2)

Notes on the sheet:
Read on D4
To GND plane (IF THERE IS ONE)
mess up order, as long as traces work!
Breaking out useful pins (cause this is a prototype)
CP on D6 MR on D7
Right-angle pins?
Plugging in an offbrand ESP32 S3 Devkit (this is a prototype)
LED Data on D5
Pin connections are arbitrary (should suit pcb)

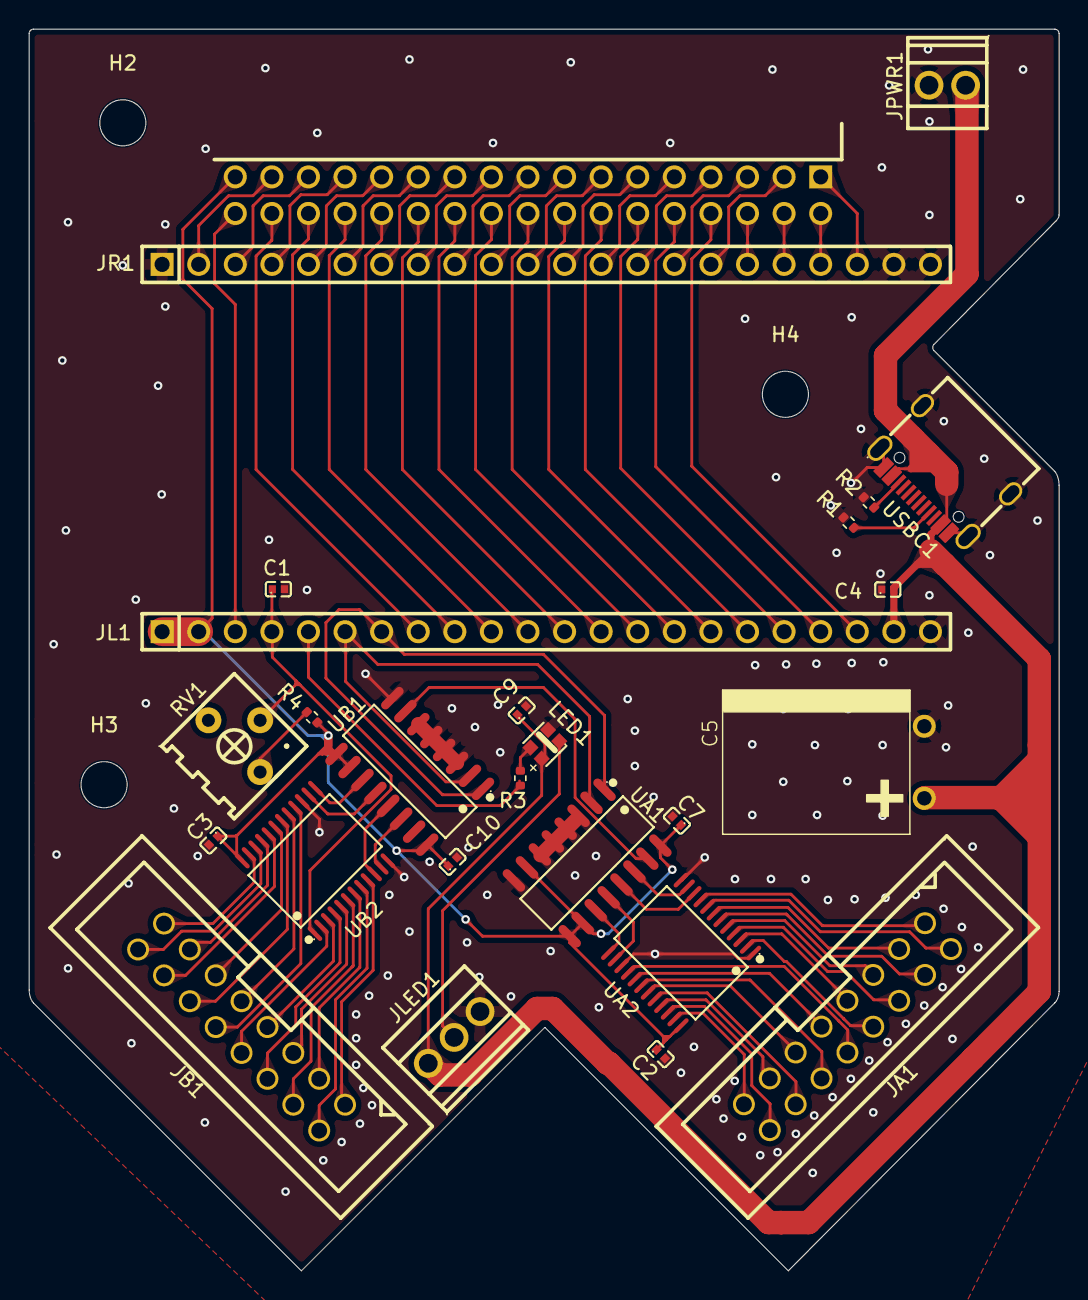
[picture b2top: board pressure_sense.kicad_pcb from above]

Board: 2 copper layers, 71.5 x 86.2 mm, 29 parts (0 on the bottom side), 86 nets.
